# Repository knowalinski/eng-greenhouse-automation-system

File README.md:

# eng-greenhouse-automation-system

cno w koncu dzieje sie wiecej xD

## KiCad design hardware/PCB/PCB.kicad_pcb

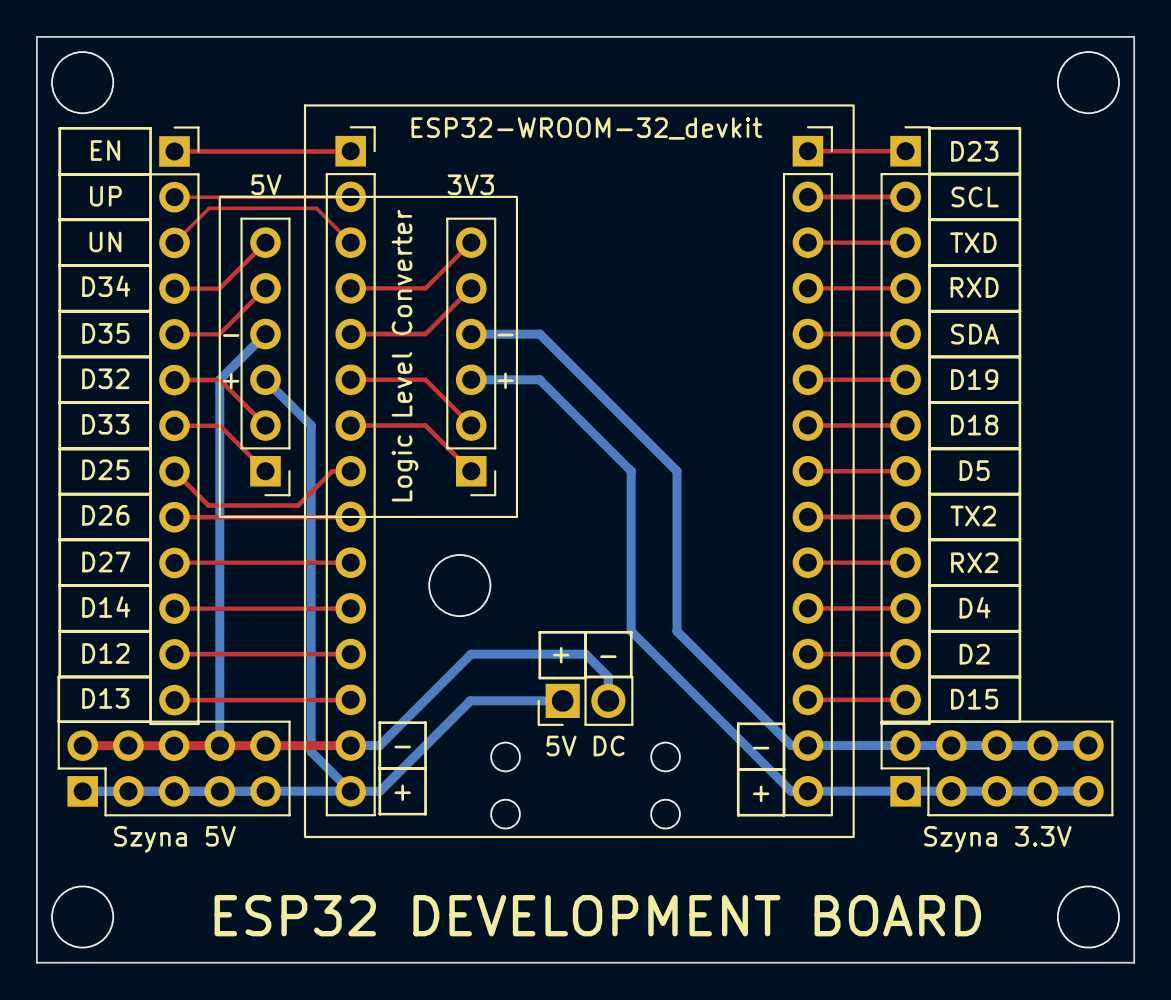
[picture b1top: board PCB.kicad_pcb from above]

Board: 2 copper layers, 61.0 x 51.4 mm, 7 parts (0 on the bottom side), 33 nets.

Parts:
5V DC: 5V DC; PinHeader_1x02_P2.54mm_Vertical
ESP32-WROOM-32_devkit: ESP32-WROOM-32_devkit; esp32-wroom-devkit-v2
J4, J5: Conn_01x13; PinSocket_1x13_P2.54mm_Vertical
Logic Level Converter: Logic_Level_Converter; logic_level_converter
Szyna 3.3V: Szyna 3.3V; PinHeader_2x05_P2.54mm_Vertical
Szyna 5V: Szyna 5V; PinHeader_2x05_P2.54mm_Vertical

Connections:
3V3: ESP32-WROOM-32_devkit.30 (3V3), Logic Level Converter.3 (LV), Szyna 3.3V.1, Szyna 3.3V.3, Szyna 3.3V.5, Szyna 3.3V.7, Szyna 3.3V.9
5V: 5V DC.1 (In), ESP32-WROOM-32_devkit.15 (VIN), Logic Level Converter.9 (HV), Szyna 5V.1, Szyna 5V.3, Szyna 5V.5, Szyna 5V.7, Szyna 5V.9
D2: ESP32-WROOM-32_devkit.27 (D2), J5.12
D4: ESP32-WROOM-32_devkit.26 (D4), J5.11
D5: ESP32-WROOM-32_devkit.23 (D5), J5.8
D12: ESP32-WROOM-32_devkit.12 (D12), J4.12
D13: ESP32-WROOM-32_devkit.13 (D13), J4.13
D14: ESP32-WROOM-32_devkit.11 (D14), J4.11
D15: ESP32-WROOM-32_devkit.28 (D15), J5.13
D18: ESP32-WROOM-32_devkit.22 (D18), J5.7
D19: ESP32-WROOM-32_devkit.21 (D19), J5.6
D23: ESP32-WROOM-32_devkit.16 (D23), J5.1
D25: ESP32-WROOM-32_devkit.8 (D25), J4.8
D26: ESP32-WROOM-32_devkit.9 (D26), J4.9
D27: ESP32-WROOM-32_devkit.10 (D27), J4.10
D32: ESP32-WROOM-32_devkit.6 (D32), Logic Level Converter.2 (LV2)
D32_H: J4.6, Logic Level Converter.8 (HV2)
D33: ESP32-WROOM-32_devkit.7 (D33), Logic Level Converter.1 (LV1)
D33_H: J4.7, Logic Level Converter.7 (HV1)
D34: ESP32-WROOM-32_devkit.4 (D34), Logic Level Converter.6 (LV4)
D34_H: J4.4, Logic Level Converter.12 (HV4)
D35: ESP32-WROOM-32_devkit.5 (D35), Logic Level Converter.5 (LV3)
D35_H: J4.5, Logic Level Converter.11 (HV3)
EN: ESP32-WROOM-32_devkit.1 (EN), J4.1
GND: 5V DC.2 (Ext), ESP32-WROOM-32_devkit.14 (GND), ESP32-WROOM-32_devkit.29 (GND), Logic Level Converter.4 (GND), Logic Level Converter.10 (GND), Szyna 3.3V.2, Szyna 3.3V.4, Szyna 3.3V.6, Szyna 3.3V.8, Szyna 3.3V.10, Szyna 5V.2, Szyna 5V.4, Szyna 5V.6, Szyna 5V.8, Szyna 5V.10
RX2: ESP32-WROOM-32_devkit.25 (RX2), J5.10
RXD: ESP32-WROOM-32_devkit.19 (RXD), J5.4
SCL: ESP32-WROOM-32_devkit.17 (D22), J5.2
SDA: ESP32-WROOM-32_devkit.20 (D21), J5.5
TX2: ESP32-WROOM-32_devkit.24 (TX2), J5.9
TXD: ESP32-WROOM-32_devkit.18 (TXD), J5.3
UN: ESP32-WROOM-32_devkit.3 (UN), J4.3
UP: ESP32-WROOM-32_devkit.2 (UP), J4.2

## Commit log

2022-12-03 test commit
2022-12-03 first test of client-server connection using http
2022-12-03 Rename gms/client.py to client.py
    cleaning
2022-12-03 Rename gms/main.py to main.py
    cleaning
2022-12-03 esp32 empty firmware commit
2022-12-04 passed first tests
2022-12-11 Add files via upload
    working prototype of keeping alive wifi usung freeRTOS tasks (oled handling used as second task to add some load to second core of esp32)
2022-12-11 Update freertos+wifi.ino
    working prototype
2022-12-11 Update freertos+wifi.ino
    comments
2022-12-11 Update client.py
    comments
2022-12-11 Update main.py
    comments
2022-12-11 Create readme
    xyz
2022-12-18 Update freertos+wifi.ino
    sending data as json
2022-12-19 Update freertos+wifi.ino
    naprawiony bug z przesyłaniem ramki danych, dodane pole z id urządzenia
2022-12-19 Update main.py
    rozwinięcie części serwerowej, dodanie loggera stanów
2022-12-28 Rename freertos+wifi.ino to freertos_wifi.ino
    "+" w nazwie to zły pomysł xD
2022-12-28 Update freertos_wifi.ino
    dodane pobieranie czasu z serwera.
    Do wyjaśnienia: problemy z przesyłaniem danych, możliwe, że przez nakładanie się tasków
2022-12-28 Update main.py
    dodane wysyłanie aktualnego czasu i podział wyników z czujników na pliki
2022-12-28 Update freertos_wifi.ino
    dodane TODO
2023-01-04 Update freertos_wifi.ino
    zabezpieczenie przed nullem v0.1
2023-01-05 Update freertos_wifi.ino
    działa zabezpieczenie
2023-01-05 Update main.py
    nawet nie wiem co tu się zmieniło xD
2023-01-05 Create csv_playground.py
    wprawki do pracy z danymi w csv
2023-01-08 Delete esp32_firmware directory
    sprzątanie
2023-01-08 Delete client.py
    sprzątanie
2023-01-08 Rename main.py to backend/main.py
    sprzątanie
2023-01-08 Rename csv_playground.py to backend/csv_playground.py
    sprzątanie
2023-01-08 Rename freertos_wifi.ino to esp32-firmware/freertos_wifi.ino
    sprzątanie
2023-01-08 Changes to be committed: new file: frontend/index.html new file: frontend/script.js new file: frontend/style.css
2023-01-08 małe poprawki wizualne
2023-01-08 dodane renderowanie html w flaskowym api dodane ścieżki do html-a i css-a
2023-01-08 podlinkowany plik js-a js dodany w strukturze flaskowej
2023-01-08 zmiana nazw + rozwinięcie backendu
2023-01-08 rozwinieta część serwerowa dodane opisy routów
2023-01-08 added .gitignore
2023-01-08 smth
2023-01-08 praca z przetwarzaniem csv
2023-01-10 praca nad dashboardem
2023-01-10 working with html generator
2023-01-11 html generator
2023-01-11 rozwój data_operator-a
2023-01-15 rozwój operacji na czasie
2023-01-16 poprawa działania DataOperatora
2023-01-18 modified: .gitignore modified: backend/main.py
2023-01-18 updated gitignore
2023-01-18 minor changes
2023-01-20 cleaning
2023-01-21 [backend] Updated data_operator and main added css class change when sensor is inactive for some time
    modified: backend/box_generator.py
    modified: backend/data_operator.py
    modified: backend/main.py
    modified: backend/templates/index.html
2023-02-01 updated git ignore and cleaning project from garbage files
2023-02-02 refactoring
2023-02-02 reafactoring
2023-02-02 updated .gitignore deleted old version of backend
2023-02-03 [frontend] added html for plotting
2023-02-03 [backend] changed template to render in plotter()
2023-02-03 [repo] cleaning
2023-02-03 [repo] updated .gitignore
2023-02-03 [backend] refactoring main.py
2023-02-03 [frontend] minor changes to index.html
2023-02-04 [backend] added timestamp handler added comments for data_operator functions
2023-02-04 [frontend] changes from html generator
2023-02-04 [backend] fixed timestemps operators
2023-02-05 [backend] added prototype function for plotting x records
2023-02-09 [hardware] added hardware documentation schema of measuring device project of development PCB
2023-02-09 [hardware] updating files
2023-02-12 [hardware] updated hardware files
2023-02-12 [paper] added draft version of paper added photos and oscilograms for hardware
2023-02-12 [paper] added diagrams updated paper
2023-02-12 [paper] added diagrams for serwer idea
2023-02-13 [paper] added renders of enclosures
2023-02-13 [hardware] added models of enclosures
2023-02-13 [paper] updated paper
2023-02-13 [frontend] updated html from generator
2023-02-13 [backend] added feedback function for communication with ESP32
2023-02-14 [hardware] updated 3d models
2023-02-19 [firmware] updated firmaware for ESP32
2023-02-19 [repo] added TODO file (in polish)
2023-02-19 [frontend] updated plotting.html - added plot for soil moisture
2023-02-19 [backend] changes for handling shorter dataframe added plot generating for soil moisture minor cleaning
2023-02-19 [repo] updated TODO list
2023-02-19 [firmware] debugging and refactoring
2023-02-19 [repo] updated TODO
2023-02-19 [paper] updated paper and added one screenshot of code
2023-02-20 [repo] added progress tracking file
2023-02-20 [tools] added execution timer and script for mocking sensors
2023-02-26 [tools] updated mock_seensor (monor refactoring)
2023-02-26 [paper] updated paper, added screen for mock_sensor code
2023-02-26 [paper] updated paper and added screenshots
2023-02-27 [paper] added photos and renders added draft diagram for api updated paper
2023-02-28 [paper] updated paper added screeshoots
2023-03-03 [backend] updated html generator and minor refactor
2023-03-03 [frontend] updated css file added generated html
2023-03-03 [hardware] updated diagram
2023-03-03 [paper] added screeshoots
2023-03-04 [frontend] cleaning
2023-03-04 [tools] minor refactoring
2023-03-04 [firmware] minor refactoring
2023-03-26 [backend] minor refactoring, added one endpoint
2023-03-26 [frontend] minor refactoring
2023-03-26 [paper] updated images lib
2023-03-26 [paper] added other documents
2023-04-02 [frontend] generated html for 2 sensors
2023-04-02 [tools] minor changes in mock sensor scropt
2023-04-02 [paper] added screens
2023-04-02 [paper] new img to lib
2023-04-02 [paper] updated paper (need reformating)
2023-06-13 [paper] added photos
2023-06-13 [paper] added all versions
2023-06-22 [paper] final version
2023-06-25 Changes to be committed: deleted: backend/main.py modified: backend/templates/index.html new file: backend/templates/index.html.bak deleted: hardware/3d_models/esp32_enclosure/esp32_enclosure_pt1.stl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
2023-06-25 Rename freertos_wifi.ino to freertos_wifi.cpp
